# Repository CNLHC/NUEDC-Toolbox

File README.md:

# 全国大学生电子设计竞赛工具箱

## 数字逻辑

### FPGA

1.DE10-Standard相关

- 实现FPGA2HPS数据传输
- 实现HPS2FPGA数据传输
- Linux下FT4232驱动

2.DE10-Nano相关

- 实现FPGA2HPS数据传输
- 实现HPS2FPGA数据传输
- Linux下FT4232驱动

### MCU

1.STM32F103C8t6

- 开发环境搭建

2.STM32F429

- 开发环境搭建

## AD/DA转换

### ADC

1.AD7606-16Bit/200KSPS

- FT4232驱动代码
- STM32驱动代码
- 测试笔记
  
2.AD9254-14Bit/150MSPS

- 测试笔记
- DE10驱动代码

3.ADS8586S-16Bit/250KSPS/单电供电双电采集

- 硬件模块
- FT4232驱动代码
- STM32驱动代码
- 测试笔记

### DAC

1.DAC8563-16Bit/200KSPS
  
- FT4232驱动代码
- STM32驱动代码
- 测试笔记

2.DAC5672-14Bit/275MSPS

- 测试笔记
- DE10驱动代码
  
TODO: 此外还需要选型一款低成本DAC用作程控
  
## 模拟信号

### 程控放大器

1.AD8367

- 测试笔记（注意测试小信号放大）

2.AD8368

- 测试笔记

### 程控衰减器

1.HMC624A: 0.5dB-31.5dB 0.5dB步进

- 测试笔记(注意测试低频性能)
- STM32驱动
- FT4232驱动

2.HMC346AMS8GE: 0-32dB 连续程控

- 测试笔记

### 低噪声放大

1.LTC6268: 单电/低噪

- 硬件设计
- 测试文档

2.ADA4522: 单电/零漂/低噪声/高至55V供电

- 评估版设计
- 测试文档

3.ADA4817: 单电/高GBP/低噪

### 功率放大器

## 无线数据传输

## 电源

### 超低纹波

### 单转双

### 大功率

## 控制台

选型一款工业级的串口HMI，一定要触屏！大触屏！

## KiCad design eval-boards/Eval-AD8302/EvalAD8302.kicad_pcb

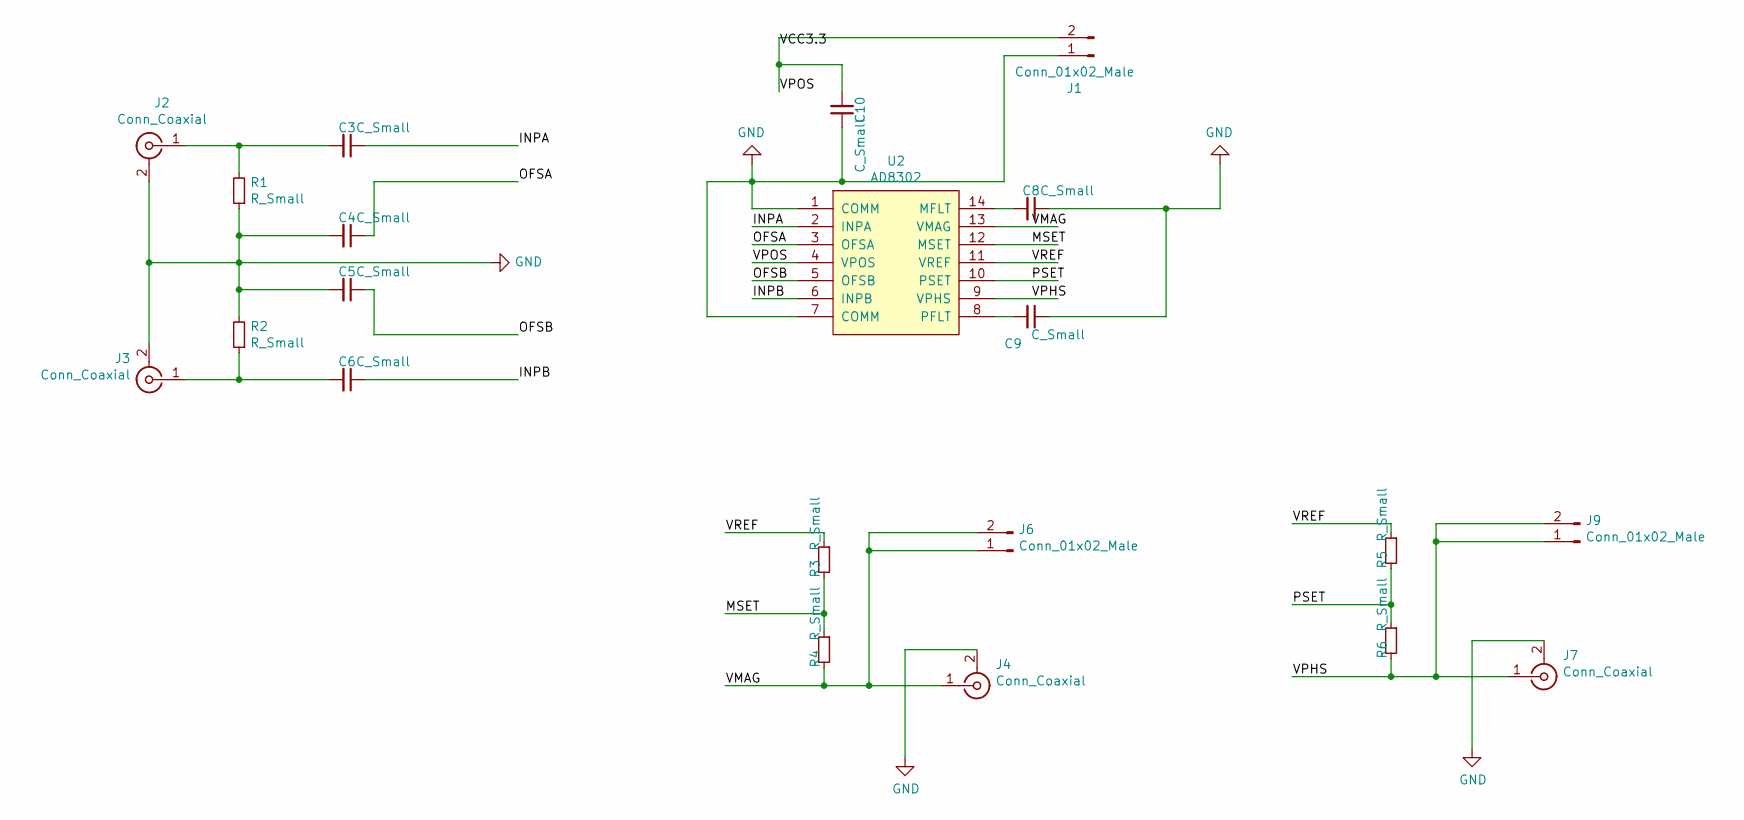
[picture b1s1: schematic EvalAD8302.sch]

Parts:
C3, C4, C5, C6, C8, C9, C10: C_Small; C_0603_1608Metric_Pad1.05x0.95mm_HandSolder
J1: Conn_01x02_Male; JST_XH_B02B-XH-A_02x2.50mm_Straight
J2, J3, J4, J7: Conn_Coaxial; SMA
J6, J9: Conn_01x02_Male; PinHeader_1x02_P2.54mm_Vertical
R1: R_Small; R_0805_2012Metric_Pad1.15x1.40mm_HandSolder
R2, R3, R4, R5, R6: R_Small; R_0805_HandSoldering
U2: AD8302; TSSOP-14_4.4x5mm_Pitch0.65mm

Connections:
/INPA: C3.1, U2.2 (INPA)
/INPB: C6.1, U2.6 (INPB)
/MSET: R3.2, R4.1, U2.12 (MSET)
/OFSA: C4.1, U2.3 (OFSA)
/OFSB: C5.1, U2.5 (OFSB)
/PSET: R5.2, R6.1, U2.10 (PSET)
/VCC3.3: C10.2, J1.2, U2.4 (VPOS)
/VMAG: J4.1 (In), J6.1, J6.2, R4.2, U2.13 (VMAG)
/VPHS: J7.1 (In), J9.1, J9.2, R6.2, U2.9 (VPHS)
/VREF: R3.1, R5.1, U2.11 (VREF)
GND: C4.2, C5.2, C8.1, C9.1, C10.1, J1.1, J2.2 (Ext), J3.2 (Ext), J4.2 (Ext), J7.2 (Ext), R1.1, R2.2, U2.1 (COMM), U2.7 (COMM)
unnamed: C3.2, J2.1 (In), R1.2
unnamed: C6.2, J3.1 (In), R2.1
unnamed: C8.2, U2.14 (MFLT)
unnamed: C9.2, U2.8 (PFLT)

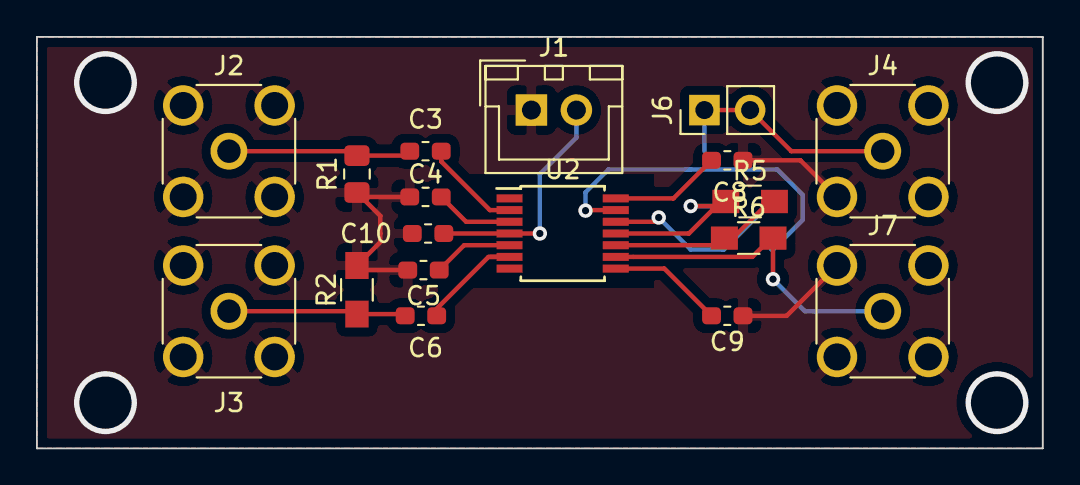
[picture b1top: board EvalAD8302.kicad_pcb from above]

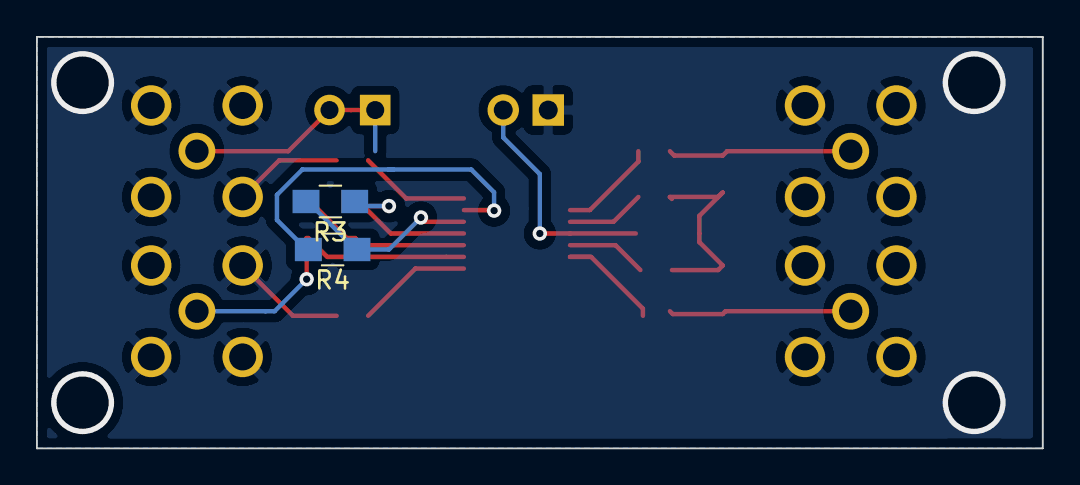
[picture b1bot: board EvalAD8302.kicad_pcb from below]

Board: 2 copper layers, 55.9 x 22.9 mm, 20 parts (2 on the bottom side), 15 nets.

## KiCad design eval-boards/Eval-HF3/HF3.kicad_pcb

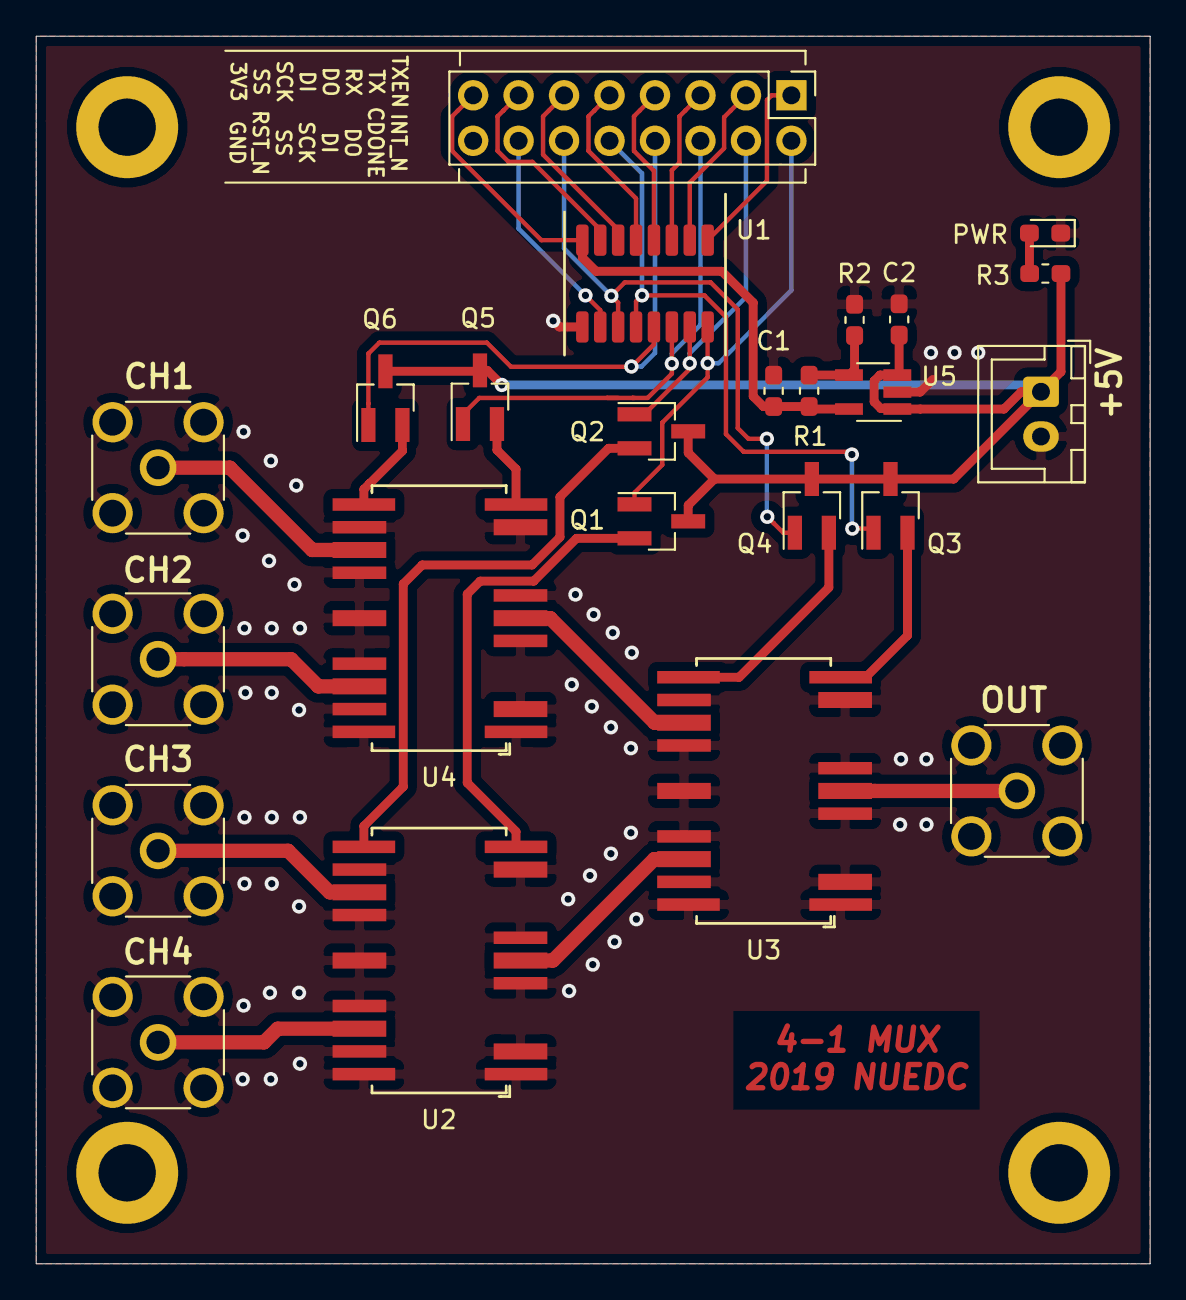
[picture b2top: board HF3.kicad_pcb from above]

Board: 2 copper layers, 62.2 x 68.6 mm, 24 parts (0 on the bottom side), 32 nets.

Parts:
+5V: Conn_01x02_Male; JST_XH_B02B-XH-A_1x02_P2.50mm_Vertical
C1, C2: 0.1u; C_0603_1608Metric_Pad1.05x0.95mm_HandSolder
CH1, CH2, CH3, CH4: Conn_Coaxial; SMA
J5: Conn_02x08_Counter_Clockwise_MountingPin; PinHeader_2x08_P2.54mm_Vertical
OUT: Conn_Coaxial; SMA
PWR: LED; LED_0603_1608Metric_Pad1.05x0.95mm_HandSolder
Q1, Q2, Q3, Q4, Q5, Q6: Q_NMOS_GSD; SOT-23_Handsoldering
R1: 6.8k; R_0603_1608Metric_Pad1.05x0.95mm_HandSolder
R2: 12k; R_0603_1608Metric_Pad1.05x0.95mm_HandSolder
R3: R; R_0603_1608Metric_Pad1.05x0.95mm_HandSolder
U1: CDPGA_B
U2, U3, U4: HF3-91; Relay_SPDT_AXICOM_HF3Series_50ohms_Pitch1.27mm_handsolder
U5: TPS73233; SOT-23-5_HandSoldering

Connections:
/5V: +5V.1, C2.2, Q1.3, Q2.3, Q3.3, Q4.3, Q5.3, Q6.3, R3.2, U5.1, U5.3
/RESET1: J5.15, Q2.1, U1.15
/RESET2: J5.13, Q6.1, U1.13
/RESET3: J5.11, Q4.1, U1.11
/SET1: J5.16, Q1.1, U1.16
/SET2: J5.14, Q5.1, U1.14
/SET3: J5.12, Q3.1, U1.12
GND: +5V.2, C1.1, C2.1, CH1.2, CH2.2, CH3.2, CH4.2, J5.9, OUT.2, PWR.1, R2.2, U1.9, U2.1, U2.2, U2.5, U2.7, U2.10, U2.13, U2.15, U2.17, U2.19, U2.21, U2.22, U3.1, U3.2, U3.5, U3.7, U3.10, U3.13, U3.15, U3.17, U3.19, U3.21, U3.22, U4.1, U4.2, U4.5, U4.7, U4.10, U4.13, U4.15, U4.17, U4.19, U4.21, U4.22, U5.2
unnamed: C1.2, J5.8, R1.1, U1.8, U5.5
unnamed: PWR.2, R3.1
unnamed: CH4.1, U2.20
unnamed: CH3.1, U2.14
unnamed: OUT.1, U3.6
unnamed: J5.1, U1.1
unnamed: J5.2, U1.2
unnamed: J5.3, U1.3
unnamed: J5.4, U1.4
unnamed: J5.5, U1.5
unnamed: J5.6, U1.6
unnamed: J5.7, U1.7
unnamed: J5.10, U1.10
unnamed: CH2.1, U4.20
unnamed: CH1.1, U4.14
unnamed: Q1.2, U2.11
unnamed: Q2.2, U2.12
unnamed: Q3.2, U3.11
unnamed: Q4.2, U3.12
unnamed: Q5.2, U4.11
unnamed: Q6.2, U4.12
unnamed: R1.2, R2.1, U5.4
unnamed: U2.6, U3.20
unnamed: U3.14, U4.6

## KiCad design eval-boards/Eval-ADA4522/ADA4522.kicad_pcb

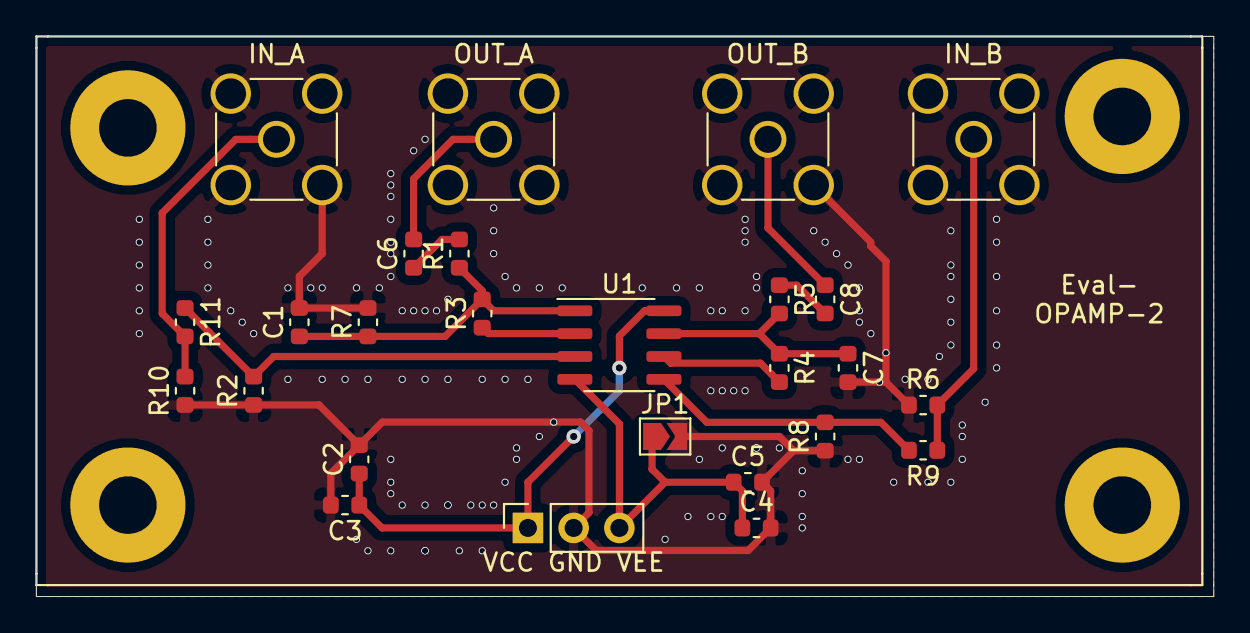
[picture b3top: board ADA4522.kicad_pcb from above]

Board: 2 copper layers, 65.4 x 31.1 mm, 26 parts (0 on the bottom side), 15 nets.

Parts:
C1, C6, C7, C8: 100pF; C_0603_1608Metric
C2, C4: 10uf; C_0603_1608Metric
C3, C5: 0.1uf; C_0603_1608Metric
IN_A: IN_A; SMA_Amphenol_132134-11_Vertical
IN_B: IN_B; SMA_Amphenol_132134-11_Vertical
JP1: SolderJumper-2_P1.3mm_Open_TrianglePad1.0x1.5mm
OUT_A: OUT_A; SMA_Amphenol_132134-11_Vertical
OUT_B: OUT_B; SMA_Amphenol_132134-11_Vertical
R1, R2, R3, R4, R5, R6, R7, R8, R9, R10, R11: R; R_0603_1608Metric
U1: ADA4522-2; SOIC-8_3.9x4.9mm_P1.27mm
VCC GND VEE: Conn_01x03_Male; PinSocket_1x03_P2.54mm_Vertical

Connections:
GND: C1.2, C2.2, C3.2, C4.2, C5.2, C7.2, IN_A.2, IN_B.2, JP1.2, OUT_A.2, OUT_B.2, R2.1, R6.1, R7.2, R8.1, R10.1, VCC GND VEE.2
unnamed: C1.1, R1.1, R3.2, R7.1, U1.1
unnamed: C2.1, C3.1, U1.8, VCC GND VEE.1
unnamed: C4.1, C5.1, JP1.1, U1.4, VCC GND VEE.3
unnamed: C6.1, R1.2
unnamed: C6.2, OUT_A.1
unnamed: C7.1, R4.1, R5.2, U1.7
unnamed: C8.1, OUT_B.1
unnamed: C8.2, R5.1
unnamed: IN_A.1, R10.2, R11.2
unnamed: IN_B.1, R6.2, R9.1
unnamed: R3.1, U1.2
unnamed: R4.2, U1.6
unnamed: R8.2, R9.2, U1.5
unnamed: R2.2, R11.1, U1.3

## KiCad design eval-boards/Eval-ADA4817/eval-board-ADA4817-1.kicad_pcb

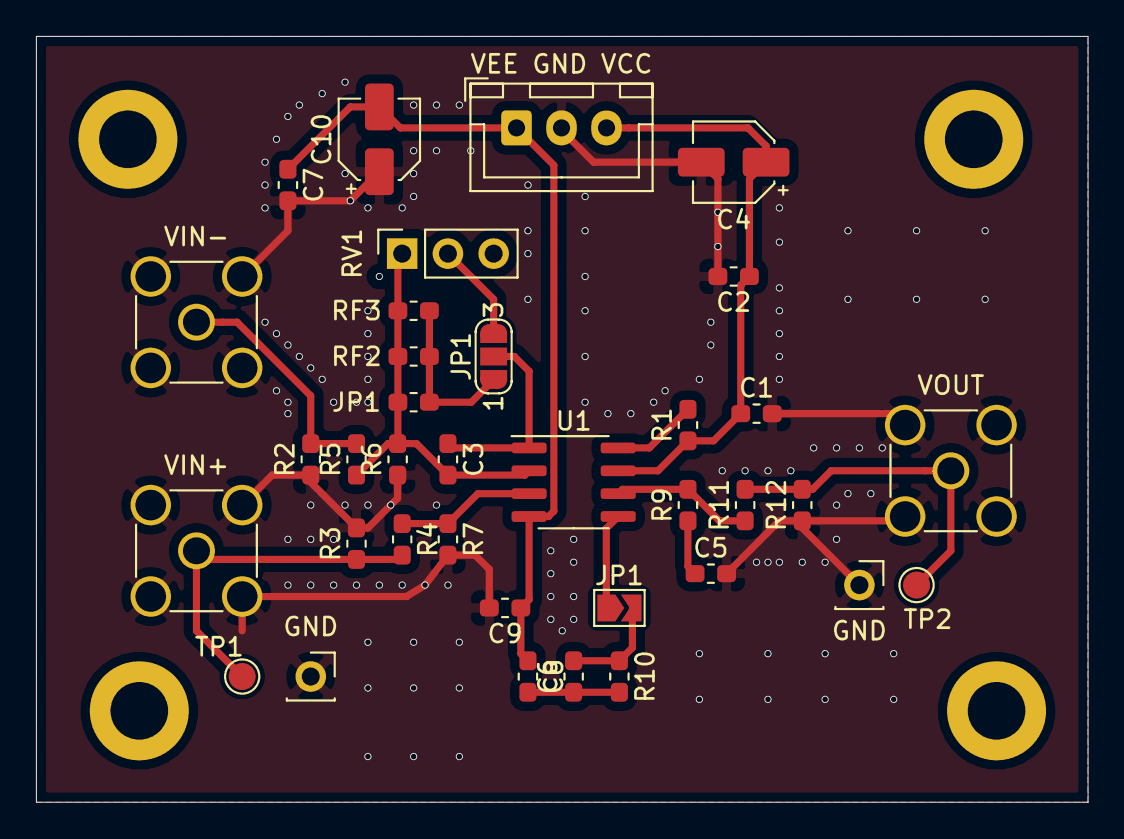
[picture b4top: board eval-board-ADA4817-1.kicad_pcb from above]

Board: 2 copper layers, 58.4 x 42.5 mm, 36 parts (0 on the bottom side), 16 nets.

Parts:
C1, C2, C7, C9: 0.1uF; C_0603_1608Metric_Pad1.05x0.95mm_HandSolder
C3: CF; C_0603_1608Metric_Pad1.05x0.95mm_HandSolder
C4, C10: 10uF; CP_Elec_4x5.4
C5: CL; C_0603_1608Metric_Pad1.05x0.95mm_HandSolder
C6, C8: C; C_0603_1608Metric_Pad1.05x0.95mm_HandSolder
GND: PinSocket_1x01_P2.54mm_Vertical
GND#2: PinSocket_1x01_P2.54mm_Vertical
JP1: SolderJumper-2_P1.3mm_Open_TrianglePad1.0x1.5mm
JP1#2: Jumper_3_Open; SolderJumper-3_P1.3mm_Open_RoundedPad1.0x1.5mm_NumberLabels
JP1#3: R; R_0603_1608Metric_Pad1.05x0.95mm_HandSolder
R1: 1kΩ; R_0603_1608Metric_Pad1.05x0.95mm_HandSolder
R2: RTN; R_0603_1608Metric_Pad1.05x0.95mm_HandSolder
R3: RTP; R_0603_1608Metric_Pad1.05x0.95mm_HandSolder
R4, R5, R6, R7, R10, R11, R12: R; R_0603_1608Metric_Pad1.05x0.95mm_HandSolder
R9: RS; R_0603_1608Metric_Pad1.05x0.95mm_HandSolder
RF2, RF3: R; R_0603_1608Metric_Pad1.05x0.95mm_HandSolder
RV1: R_POT; PinSocket_1x03_P2.54mm_Vertical
TP1, TP2: TestPoint_Pad_D1.5mm
U1: ADA4817-1; SOIC-8_3.9x4.9mm_P1.27mm
VEE GND VCC: Conn_01x03_Male; JST_XH_B3B-XH-A_1x03_P2.50mm_Vertical
VIN+: +VIN; SMA_Amphenol_132134-11_Vertical
VIN-: -VIN; SMA_Amphenol_132134-11_Vertical
VOUT: VOUT; SMA_Amphenol_132134-11_Vertical

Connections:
/PD: R1.2, U1.8
/VCC: C1.1, C2.1, C4.1, R1.1, U1.7, VEE GND VCC.3
/VEE: C7.1, C8.1, C9.1, C10.2, U1.4, VEE GND VCC.1
GNDREF: C1.2, C2.2, C4.2, C5.2, C7.2, C9.2, C10.1, GND.1, GND#2.1, R2.1, R3.2, R6.1, R7.2, R12.1, VEE GND VCC.2, VIN+.2, VIN-.2, VOUT.2
unnamed: C3.1, JP1#2.2, U1.1
unnamed: C3.2, JP1#3.1, R5.1, R6.2, RF2.1, RF3.2, RV1.1, U1.2
unnamed: C5.1, R9.1
unnamed: C6.1, C8.2, R10.2
unnamed: C6.2, JP1.1, JP1.2, R10.1, U1.5
unnamed: R2.2, R5.2, VIN-.1
unnamed: R3.1, R4.2, TP1.1, VIN+.1
unnamed: R11.2, R12.2, TP2.1, VOUT.1
unnamed: JP1#2.1, JP1#3.2, RF2.2, RF3.1
unnamed: JP1#2.3, RV1.2
unnamed: R4.1, R7.1, U1.3
unnamed: R9.2, R11.1, U1.6

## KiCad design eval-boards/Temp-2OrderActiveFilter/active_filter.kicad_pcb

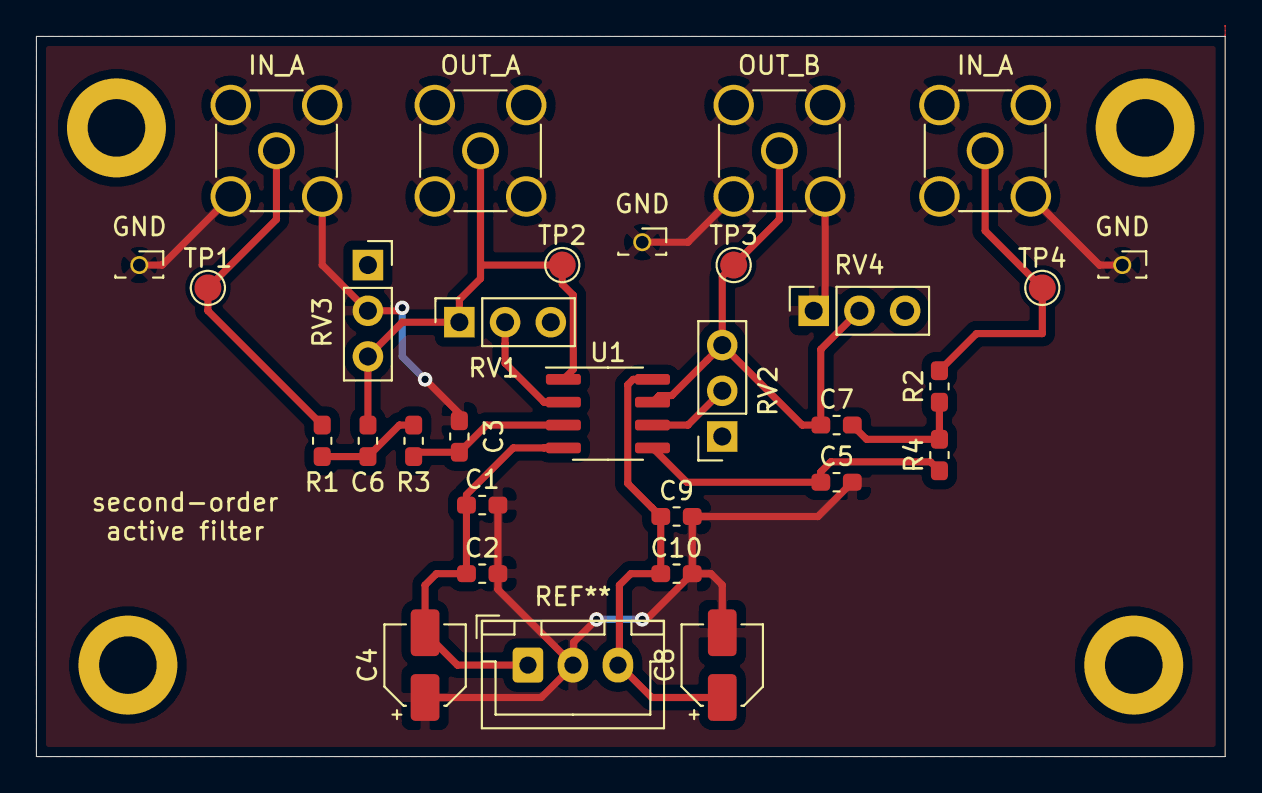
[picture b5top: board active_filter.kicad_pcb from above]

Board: 2 copper layers, 66.0 x 40.0 mm, 30 parts (0 on the bottom side), 13 nets.

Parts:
C1, C2: 0.1uf; C_0603_1608Metric_Pad1.05x0.95mm_HandSolder
C3, C5, C6, C7: C; C_0603_1608Metric_Pad1.05x0.95mm_HandSolder
C4, C8: 10uF; CP_Elec_4x5.3
C9, C10: 0.1uF; C_0603_1608Metric_Pad1.05x0.95mm_HandSolder
GND: PinSocket_1x01_P1.27mm_Vertical
GND#2, GND#3: PinSocket_1x01_P1.27mm_Vertical
IN_A: IN_A; SMA_Amphenol_132134-11_Vertical
IN_A#2: IN_B; SMA_Amphenol_132134-11_Vertical
OUT_A: OUT_A; SMA_Amphenol_132134-11_Vertical
OUT_B: OUT_B; SMA_Amphenol_132134-11_Vertical
R1, R2, R3, R4: R; R_0603_1608Metric_Pad1.05x0.95mm_HandSolder
RV1, RV2, RV3, RV4: PinSocket_1x03_P2.54mm_Vertical
TP1, TP2, TP3, TP4: TestPoint_Pad_D1.5mm
U1: ADA4075-2; SOIC-8_3.9x4.9mm_P1.27mm

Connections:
/VCC: C8.1, C9.1, C10.1, U1.8
/VEE: C1.1, C2.1, C4.2, U1.4
GND: C1.2, C2.2, C3.2, C4.1, C5.2, C8.2, C9.2, C10.2, GND.1, GND#2.1, GND#3.1, IN_A.2, IN_A#2.2, OUT_A.2, OUT_B.2, RV3.2, RV4.1
unnamed: C3.1, R3.1, U1.3
unnamed: C5.1, R4.1, U1.5
unnamed: C6.1, OUT_A.1, RV1.1, RV3.3, TP2.1, U1.1
unnamed: C6.2, R1.1, R3.2
unnamed: C7.1, OUT_B.1, RV2.3, RV4.2, TP3.1, U1.7
unnamed: C7.2, R2.1, R4.2
unnamed: IN_A.1, R1.2, TP1.1
unnamed: IN_A#2.1, R2.2, TP4.1
unnamed: RV1.2, U1.2
unnamed: RV2.2, U1.6

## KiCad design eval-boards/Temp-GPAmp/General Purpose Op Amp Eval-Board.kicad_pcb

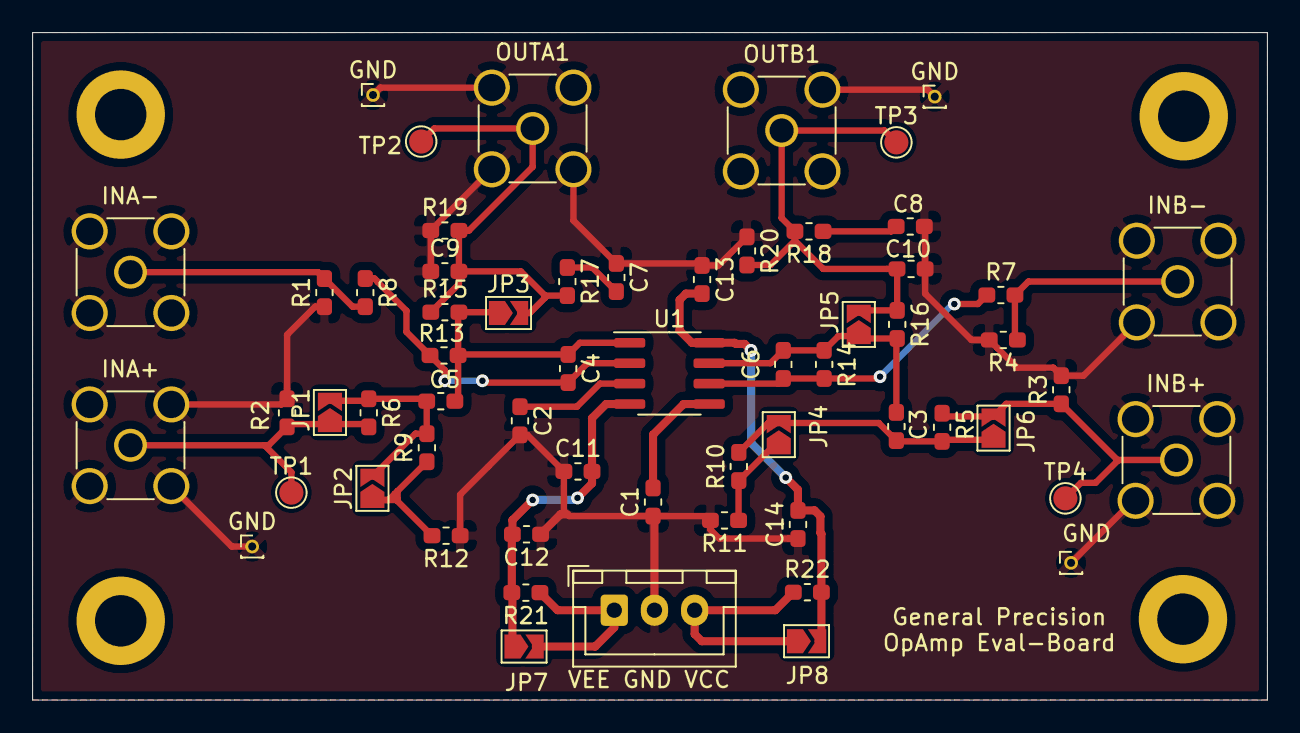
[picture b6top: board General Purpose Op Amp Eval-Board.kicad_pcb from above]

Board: 2 copper layers, 76.8 x 41.5 mm, 60 parts (0 on the bottom side), 23 nets.

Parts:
C1, C2, C3, C4, C5, C6, C7, C8, C9, C10, C11, C12, C13, C14: C; C_0603_1608Metric_Pad1.05x0.95mm_HandSolder
GND: PinHeader_1x01_P1.00mm_Vertical
GND#2, GND#3, GND#4: PinHeader_1x01_P1.00mm_Vertical
INA+: Conn_Coaxial; SMA_Amphenol_132134-11_Vertical
INA-: Conn_Coaxial; SMA_Amphenol_132134-11_Vertical
INB+: Conn_Coaxial; SMA_Amphenol_132134-11_Vertical
INB-: Conn_Coaxial; SMA_Amphenol_132134-11_Vertical
JP1, JP2, JP3, JP4, JP5, JP6, JP7, JP8: SolderJumper-2_P1.3mm_Open_TrianglePad1.0x1.5mm
OUTA1: Conn_Coaxial; SMA_Amphenol_132134-11_Vertical
OUTB1: Conn_Coaxial; SMA_Amphenol_132134-11_Vertical
R1, R2, R3, R4, R5, R6, R7, R8, R9, R10, R11, R12, R13, R14, R15, R16, R17, R18, R19, R20, R21, R22: R; R_0603_1608Metric_Pad1.05x0.95mm_HandSolder
TP1, TP2, TP3, TP4: TestPoint_Pad_D1.5mm
U1: ADA4075-2; SOIC-8_3.9x4.9mm_P1.27mm
VEE GND VCC: Conn_01x03_Male; JST_XH_B3B-XH-A_1x03_P2.50mm_Vertical

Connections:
/VCC: JP8.1, R22.1, VEE GND VCC.3
/VEE: JP7.2, R21.1, VEE GND VCC.1
GND: C1.1, C2.2, C7.1, C8.1, C9.1, C10.1, C11.1, C12.1, C13.1, C14.1, GND.1, GND#2.1, GND#3.1, GND#4.1, INA+.2, INA-.2, INB+.2, INB-.2, OUTA1.2, OUTB1.2, R1.1, R2.1, R3.2, R4.2, R11.2, R12.1, R19.1, R20.1, VEE GND VCC.2
unnamed: C1.2, U1.5
unnamed: C2.1, U1.3
unnamed: C3.1, C6.1, JP5.1, R14.1, R16.2, U1.7
unnamed: C3.2, JP4.2, JP6.1, R5.1, R10.2
unnamed: C4.1, C5.1, JP3.1, R13.1, R15.2, U1.1
unnamed: C4.2, R8.1, R13.2, U1.2
unnamed: C5.2, JP1.2, JP2.2, R6.1, R9.2
unnamed: C6.2, R7.1, R14.2, U1.6
unnamed: C7.2, R17.1
unnamed: C8.2, R18.1
unnamed: C9.2, JP3.2, OUTA1.1, R15.1, R17.2, R19.2, TP2.1
unnamed: C10.2, JP5.2, OUTB1.1, R16.1, R18.2, R20.2, TP3.1
unnamed: C11.2, C12.2, JP7.1, R21.2, U1.4
unnamed: C13.2, C14.2, JP8.2, R22.2, U1.8
unnamed: INA+.1, JP1.1, R2.2, R6.2, TP1.1
unnamed: INA-.1, R1.2, R8.2
unnamed: INB+.1, JP6.2, R3.1, R5.2, TP4.1
unnamed: INB-.1, R4.1, R7.2
unnamed: JP4.1, R10.1, R11.1
unnamed: JP2.1, R9.1, R12.2

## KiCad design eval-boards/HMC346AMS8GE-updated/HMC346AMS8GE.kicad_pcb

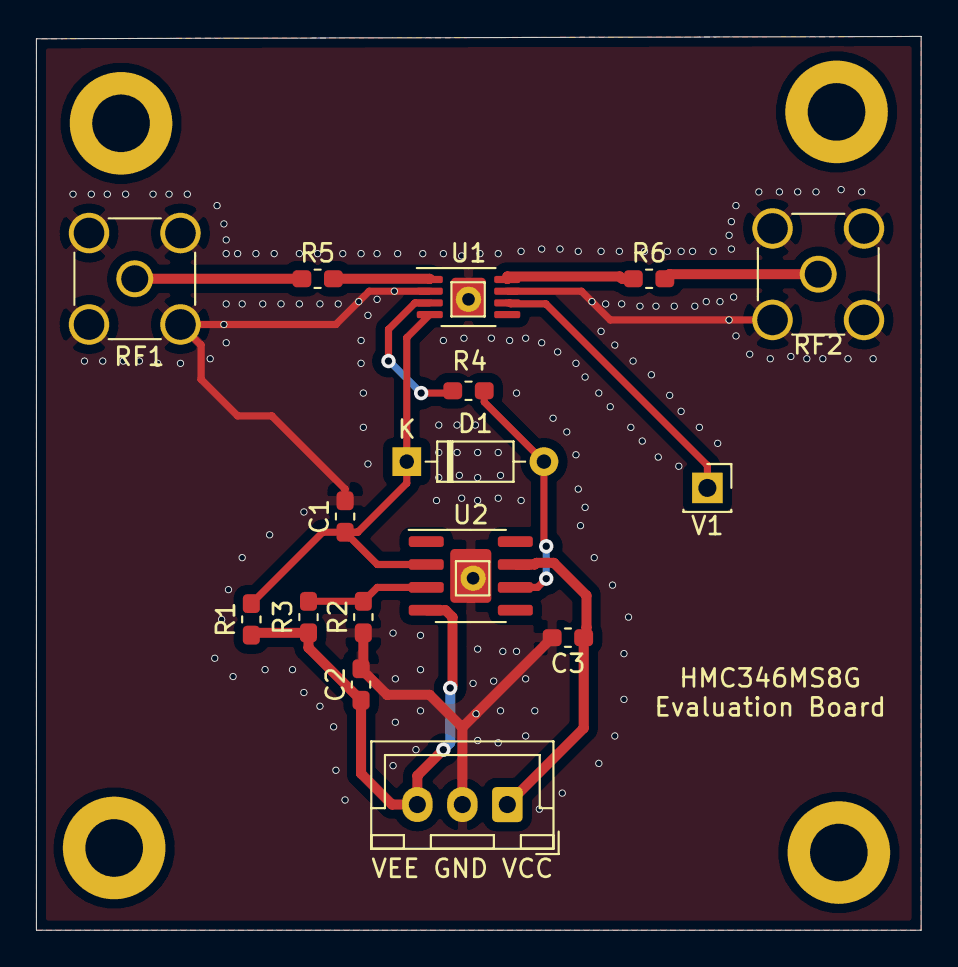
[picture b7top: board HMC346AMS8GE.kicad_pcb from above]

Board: 2 copper layers, 49.1 x 49.7 mm, 16 parts (0 on the bottom side), 12 nets.

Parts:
C1, C2, C3: C; C_0603_1608Metric_Pad1.05x0.95mm_HandSolder
D1: 1N4148; D_DO-35_SOD27_P7.62mm_Horizontal
R1, R3: 3.92k; R_0603_1608Metric_Pad1.05x0.95mm_HandSolder
R2: 500; R_0603_1608Metric_Pad1.05x0.95mm_HandSolder
R4, R5, R6: R; R_0603_1608Metric_Pad1.05x0.95mm_HandSolder
RF1, RF2: Conn_Coaxial; SMA_Amphenol_901-144_Vertical
U1: HMC346AMS8GE; MSOP-8-1EP_3x3mm_P0.65mm_EP1.95x2.15mm
U2: THS4631D; SOIC-8-1EP_3.9x4.9mm_P1.27mm_EP2.29x3mm
V1: Conn_01x01_Male; PinSocket_1x01_P2.54mm_Vertical
VEE GND VCC: Conn_01x03_Male; JST_XH_B3B-XH-A_1x03_P2.50mm_Vertical

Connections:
/I: C1.1, D1.1, R1.2, U1.4, U2.2
/V1: U1.6, V1.1
/V2: R4.2, U1.3
/VCC: C3.1, U2.7, VEE GND VCC.1
/VEE: C2.1, R1.1, R3.1, U2.4, VEE GND VCC.3
GND: C1.2, C2.2, C3.2, R2.1, RF1.2, RF2.2, U1.2, U1.7, U1.9, U2.9, VEE GND VCC.2
unnamed: D1.2, R4.1, U2.6
unnamed: R5.1, RF1.1
unnamed: R6.2, RF2.1
unnamed: R2.2, R3.2, U2.3
unnamed: R5.2, U1.1
unnamed: R6.1, U1.8

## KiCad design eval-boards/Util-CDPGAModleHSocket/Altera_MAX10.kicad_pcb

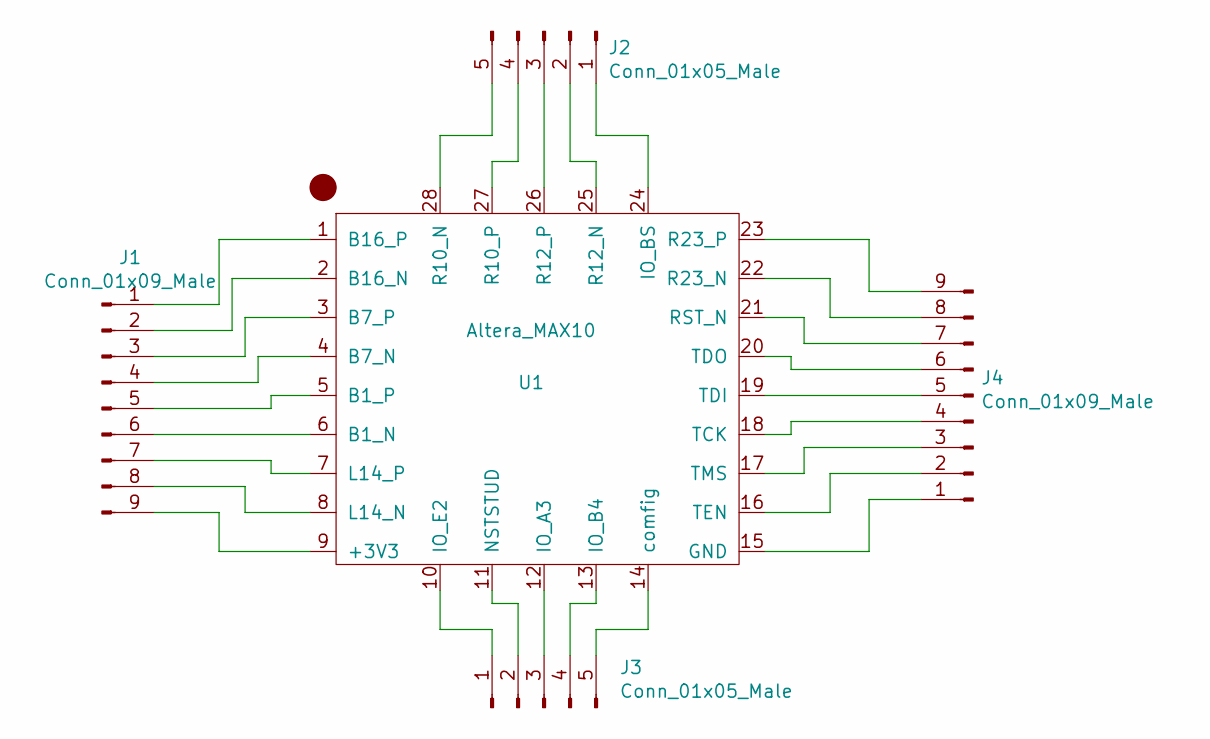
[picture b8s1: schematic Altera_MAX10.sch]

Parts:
J1, J4: Conn_01x09_Male; PinSocket_1x09_P2.54mm_Vertical
J2, J3: Conn_01x05_Male; PinSocket_1x05_P2.54mm_Vertical
U1: Altera_MAX10

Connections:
unnamed: J1.1, U1.1 (B16_P)
unnamed: J1.2, U1.2 (B16_N)
unnamed: J1.3, U1.3 (B7_P)
unnamed: J1.4, U1.4 (B7_N)
unnamed: J1.5, U1.5 (B1_P)
unnamed: J1.6, U1.6 (B1_N)
unnamed: J1.7, U1.7 (L14_P)
unnamed: J1.8, U1.8 (L14_N)
unnamed: J1.9, U1.9 (+3V3)
unnamed: J2.1, U1.24 (IO_BS)
unnamed: J2.2, U1.25 (R12_N)
unnamed: J2.3, U1.26 (R12_P)
unnamed: J2.4, U1.27 (R10_P)
unnamed: J2.5, U1.28 (R10_N)
unnamed: J3.1, U1.10 (IO_E2)
unnamed: J3.2, U1.11 (NSTSTUD)
unnamed: J3.3, U1.12 (IO_A3)
unnamed: J3.4, U1.13 (IO_B4)
unnamed: J3.5, U1.14 (comfig)
unnamed: J4.1, U1.15 (GND)
unnamed: J4.2, U1.16 (TEN)
unnamed: J4.3, U1.17 (TMS)
unnamed: J4.4, U1.18 (TCK)
unnamed: J4.5, U1.19 (TDI)
unnamed: J4.6, U1.20 (TDO)
unnamed: J4.7, U1.21 (RST_N)
unnamed: J4.8, U1.22 (R23_N)
unnamed: J4.9, U1.23 (R23_P)

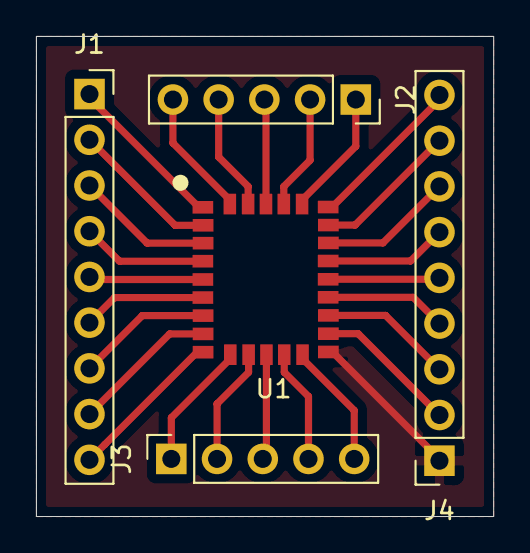
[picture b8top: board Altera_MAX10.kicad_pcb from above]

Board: 2 copper layers, 25.4 x 26.7 mm, 5 parts (0 on the bottom side), 28 nets.

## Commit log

2019-06-30 更新目录
2019-07-01 建立基本目录结构
2019-07-01 整理目录结构，删除testmain中的typo
2019-07-01 整理 stm32驱动目录
2019-07-02 整理目录
2019-07-03 general driver framework development
2019-07-03 final vision
    最终版
2019-07-03 General Purpose Op Amp Eval-Board
    仅原理图版本，芯片单运放SIOC-8封装
2019-07-04 eval-GP-board
2019-07-04 Updated schematic
    均采用双运放，前级4522可以单运放工作也可以级联工作
2019-07-04 first edition PCB
    复杂度有点高。。。画的有点晕，问题很大
2019-07-04 eval-ADA4522-2
    ADA4522-2的通用评测板
2019-07-05 eval-board-ADA4817-1
    找到了官方评估板（LFCSP封装的），改成SOIC
    也可以做其它类似单运放的通用板
2019-07-05 整理驱动代码，迁移至STM32F429开发板
2019-07-06 update-version
2019-07-06 second-order_active_filter
2019-07-06 完成SPI驱动迁移(在9910下测试)
2019-07-06 验证VISA控制仪器
2019-07-06 添加GPIO抽象层
2019-07-06 修改目录结构，并完成AD9910 testcase 编写
2019-07-07 添加基于STM32F1 HAL的 GPIO 抽象层实现
2019-07-07 完成SPI抽象层编写，并使用9910测试
2019-07-08 power_and_RF_updated
    修正了ADA4817和有源滤波器的电源线管脚、反馈电阻和焊盘handsold
2019-07-08 双通道通用精密放大器PCB
2019-07-11 重新绘制了HMC346和通用高精度运放评估板
    均已提交工厂
2019-07-11 测试文档
2019-07-11 Add AMC1301 test note
2019-07-11 Try to upload test pics
2019-07-16 HMC346MS8GE_test_document
2019-07-16 HMC346MS8GE
2019-07-16 Add AD637 test note
2019-07-16 fix format problems
2019-07-17 single_AM_eval_board
2019-07-18 single-OP-AMP-eval-board-updated
2019-07-20 完成9910 4232侧回归测试
2019-07-20 完成7606驱动并在FTD4232测试
2019-07-21 SPI_Hub
2019-07-21 完成可以和Keil link的编译配置
2019-07-22 updated_LTC6268_test_document
2019-07-23 ADA4817-1_test_document
2019-07-24 OPA695_test_document
2019-07-24 AD8009_test_document
2019-07-25 AD8099_test_document
2019-07-26 Altera_MAX10
2019-07-26 添加collectlib脚本, 删除文件名中的空格
2019-07-26 更新线路板命名规范“
2019-07-26 修改目录
2019-07-26 在文件名添加斜杠
2019-07-26 Rfc naming convention (#27)
    命名规范修改
2019-08-03 AD7606模块连接成功
2019-08-03 refactor
2019-08-03 update_Summary_of_OP_AMP
2019-08-03 完成9910驱动移植
2019-08-03 DAC8563驱动移植f4 center
2019-08-03 add 4-1 mux
2019-08-03 完成AD9959模块驱动并调试
2019-08-04 AD9959增加复位逻辑
2019-08-04 Review_Version
2019-08-05 create_Report_template
2019-08-06 add_OPA690_to_summary
